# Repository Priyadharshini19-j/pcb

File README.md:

View this project on [CADLAB.io](https://cadlab.io/project/29156). 

# pcb

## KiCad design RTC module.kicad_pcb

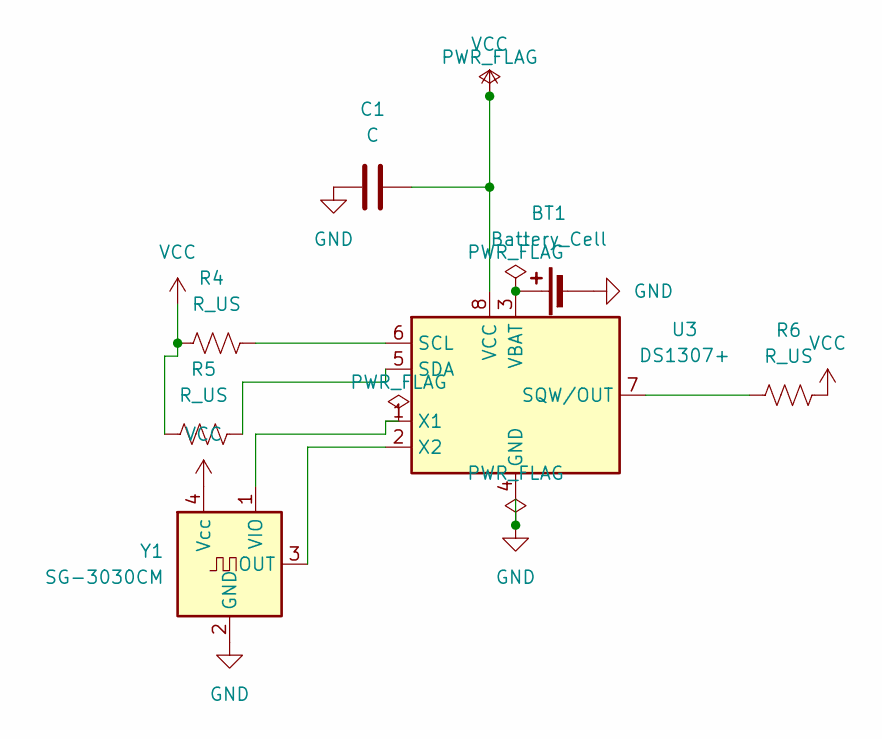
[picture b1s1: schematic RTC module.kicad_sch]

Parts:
BT1: Battery_Cell; BatteryHolder_Bulgin_BX0036_1xC
C1: C; C_0402_1005Metric
R4: R_US; R_LDR_4.9x4.2mm_P2.54mm_Vertical
R5: R_US; R_LDR_5.1x4.3mm_P3.4mm_Vertical
R6: R_US; R_LDR_5.2x5.2mm_P3.5mm_Horizontal
U3: DS1307+; DIP-8_W7.62mm
Y1: SG-3030CM; Oscillator_SMD_SeikoEpson_SG3030CM

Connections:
GND: BT1.2 (-), C1.1, U3.4 (GND), Y1.2 (GND)
unnamed: BT1.1 (+), U3.3 (VBAT)
unnamed: R4.2, U3.6 (SCL)
unnamed: R5.2, U3.5 (SDA)
unnamed: R6.1, U3.7 (SQW/OUT)
unnamed: U3.1 (X1), Y1.1 (VIO)
unnamed: U3.2 (X2), Y1.3 (OUT)
VCC: C1.2, R4.1, R5.1, R6.2, U3.8 (VCC), Y1.4 (Vcc)

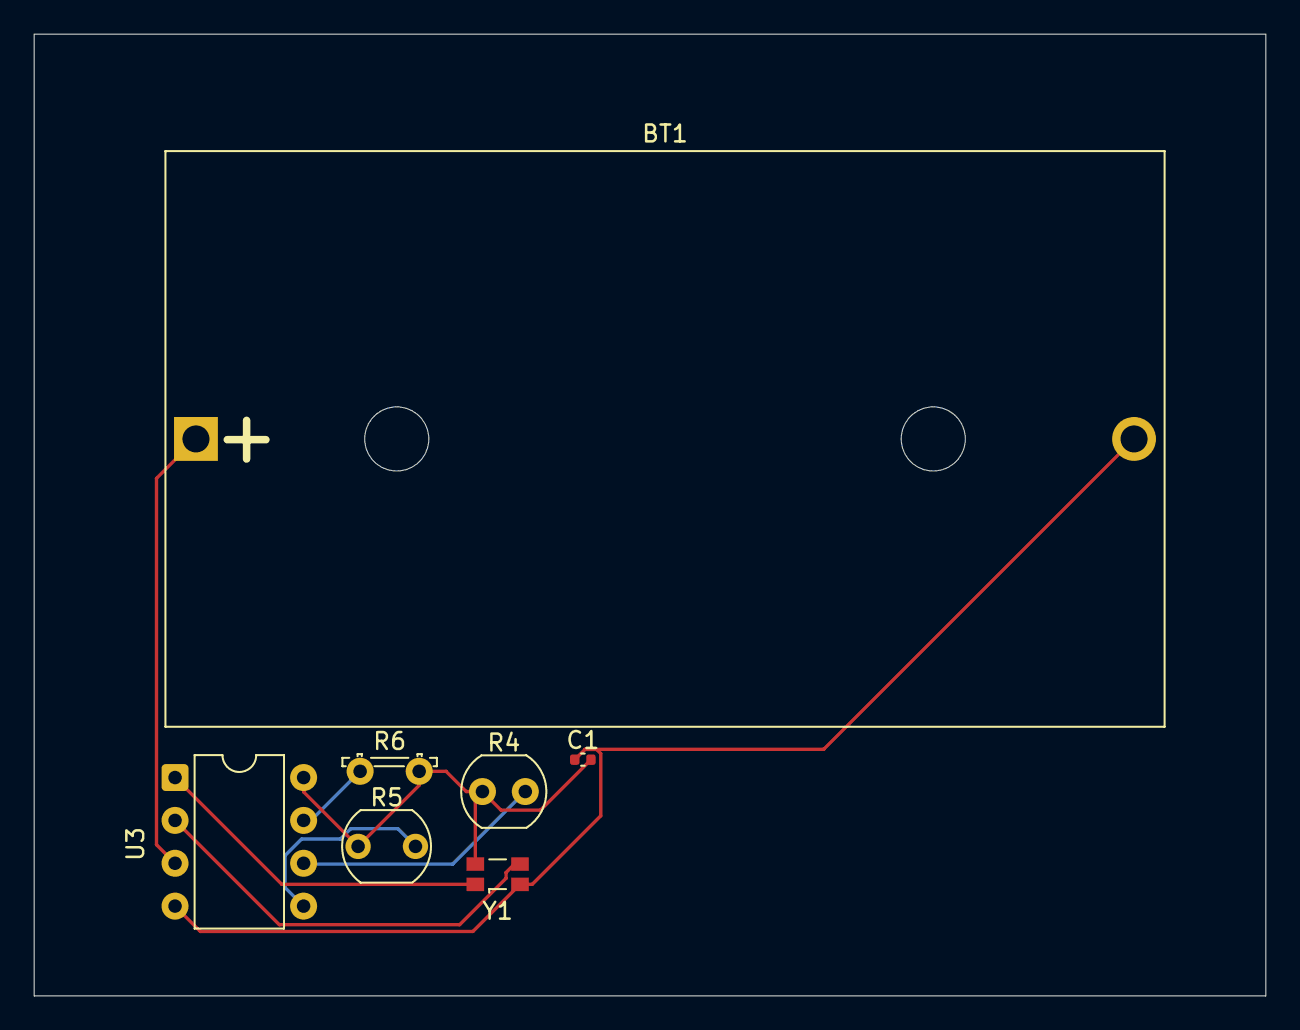
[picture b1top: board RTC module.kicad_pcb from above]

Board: 2 copper layers, 73.0 x 57.0 mm, 7 parts (0 on the bottom side), 8 nets.

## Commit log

2025-04-03 pcd_design
2025-04-03 Backlink to CADLAB.io has been added.
